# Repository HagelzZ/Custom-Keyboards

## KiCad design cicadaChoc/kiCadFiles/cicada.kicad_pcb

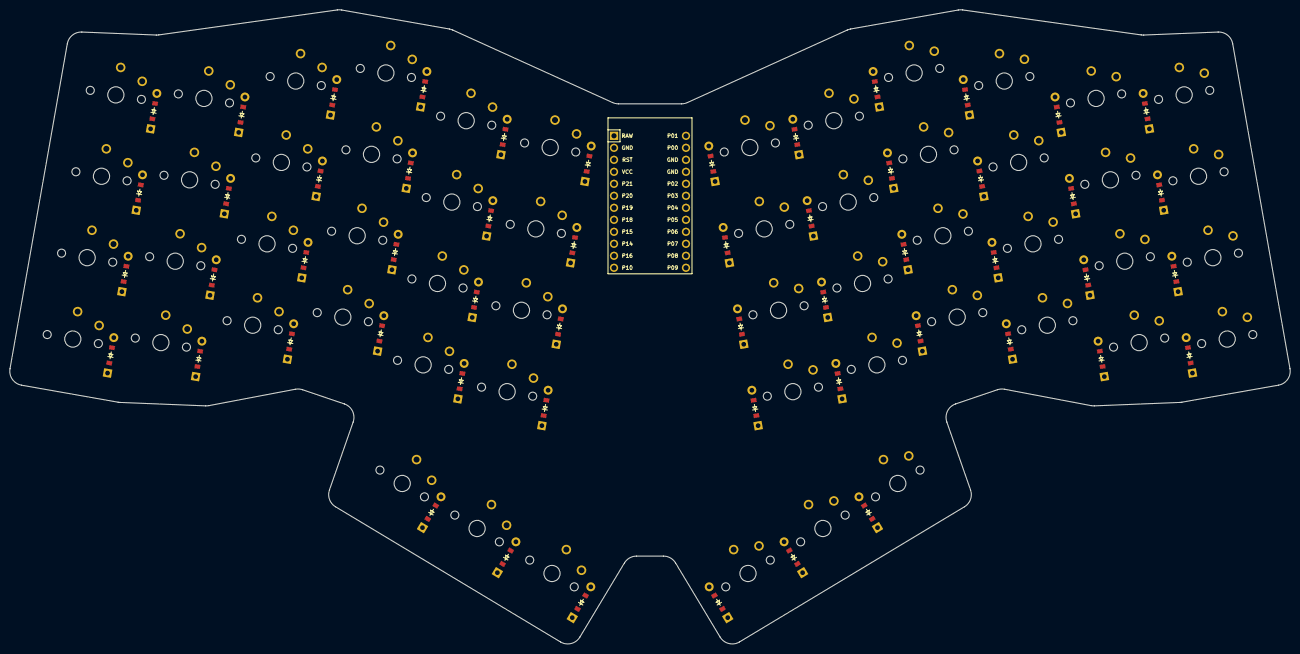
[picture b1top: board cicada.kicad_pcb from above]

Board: 2 copper layers, 271.1 x 134.3 mm, 109 parts (0 on the bottom side), 71 nets, no tracks yet.

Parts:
D1, D2, D3, D4, D5, D6, D7, D8, D9, D10, D11, D12, D13, D14, D15, D16, D17, D18, D19, D20, D21, D22, D23, D24, D25, D26, D27, D28, D29, D30, D31, D32, D33, D34, D35, D36, D37, D38, D39, D40, D41, D42, D43, D44, D45, D46, D47, D48, D49, D50, D51, D52, D53, D54: ComboDiode
MCU1: ProMicro
S1, S2, S3, S4, S5, S6, S7, S8, S9, S10, S11, S12, S13, S14, S15, S16, S17, S18, S19, S20, S21, S22, S23, S24, S25, S26, S27, S28, S29, S30, S31, S32, S33, S34, S35, S36, S37, S38, S39, S40, S41, S42, S43, S44, S45, S46, S47, S48, S49, S50, S51, S52, S53, S54: PG1350

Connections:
GND: MCU1.2, MCU1.15, MCU1.16
P0: MCU1.14, S17.1, S18.1, S19.1, S20.1, S26.1, S44.1, S45.1, S46.1, S47.1, S53.1
P1: MCU1.13, S21.1, S22.1, S23.1, S24.1, S27.1, S48.1, S49.1, S50.1, S51.1, S54.1
P2: MCU1.17, S13.1, S14.1, S15.1, S16.1, S25.1, S40.1, S41.1, S42.1, S43.1, S52.1
P3: MCU1.18, S9.1, S10.1, S11.1, S12.1, S36.1, S37.1, S38.1, S39.1
P5: D31.1, D35.1, D39.1, D43.1, D47.1, D51.1, MCU1.20
P6: D30.1, D34.1, D38.1, D42.1, D46.1, D50.1, MCU1.21
P7: D29.1, D33.1, D37.1, D41.1, D45.1, D49.1, MCU1.22
P8: D28.1, D32.1, D36.1, D40.1, D44.1, D48.1, MCU1.23
P9: D52.1, D53.1, D54.1, MCU1.24
P10: D25.1, D26.1, D27.1, MCU1.12
P14: D2.1, D6.1, D10.1, D14.1, D18.1, D22.1, MCU1.10
P15: D3.1, D7.1, D11.1, D15.1, D19.1, D23.1, MCU1.9
P16: D1.1, D5.1, D9.1, D13.1, D17.1, D21.1, MCU1.11
P18: D4.1, D8.1, D12.1, D16.1, D20.1, D24.1, MCU1.8
P20: MCU1.6, S1.1, S2.1, S3.1, S4.1, S28.1, S29.1, S30.1, S31.1
P21: MCU1.5, S5.1, S6.1, S7.1, S8.1, S32.1, S33.1, S34.1, S35.1
far_thumb: D27.2, S27.2
home_thumb: D26.2, S26.2
index_bottom: D17.2, S17.2
index_home: D18.2, S18.2
index_number: D20.2, S20.2
index_top: D19.2, S19.2
indexfar_bottom: D21.2, S21.2
indexfar_home: D22.2, S22.2
indexfar_number: D24.2, S24.2
indexfar_top: D23.2, S23.2
middle_bottom: D13.2, S13.2
middle_home: D14.2, S14.2
middle_number: D16.2, S16.2
middle_top: D15.2, S15.2
mirror_far_thumb: D54.2, S54.2
mirror_home_thumb: D53.2, S53.2
mirror_index_bottom: D44.2, S44.2
mirror_index_home: D45.2, S45.2
mirror_index_number: D47.2, S47.2
mirror_index_top: D46.2, S46.2
mirror_indexfar_bottom: D48.2, S48.2
mirror_indexfar_home: D49.2, S49.2
mirror_indexfar_number: D51.2, S51.2
mirror_indexfar_top: D50.2, S50.2
mirror_middle_bottom: D40.2, S40.2
mirror_middle_home: D41.2, S41.2
mirror_middle_number: D43.2, S43.2
mirror_middle_top: D42.2, S42.2
mirror_near_thumb: D52.2, S52.2
mirror_outer_bottom: D28.2, S28.2
mirror_outer_home: D29.2, S29.2
mirror_outer_number: D31.2, S31.2
mirror_outer_top: D30.2, S30.2
mirror_pinky_bottom: D32.2, S32.2
mirror_pinky_home: D33.2, S33.2
mirror_pinky_number: D35.2, S35.2
mirror_pinky_top: D34.2, S34.2
mirror_ring_bottom: D36.2, S36.2
mirror_ring_home: D37.2, S37.2
mirror_ring_number: D39.2, S39.2
mirror_ring_top: D38.2, S38.2
near_thumb: D25.2, S25.2
outer_bottom: D1.2, S1.2
outer_home: D2.2, S2.2
outer_number: D4.2, S4.2
outer_top: D3.2, S3.2
pinky_bottom: D5.2, S5.2
pinky_home: D6.2, S6.2
pinky_number: D8.2, S8.2
pinky_top: D7.2, S7.2
ring_bottom: D9.2, S9.2
ring_home: D10.2, S10.2
ring_number: D12.2, S12.2
ring_top: D11.2, S11.2

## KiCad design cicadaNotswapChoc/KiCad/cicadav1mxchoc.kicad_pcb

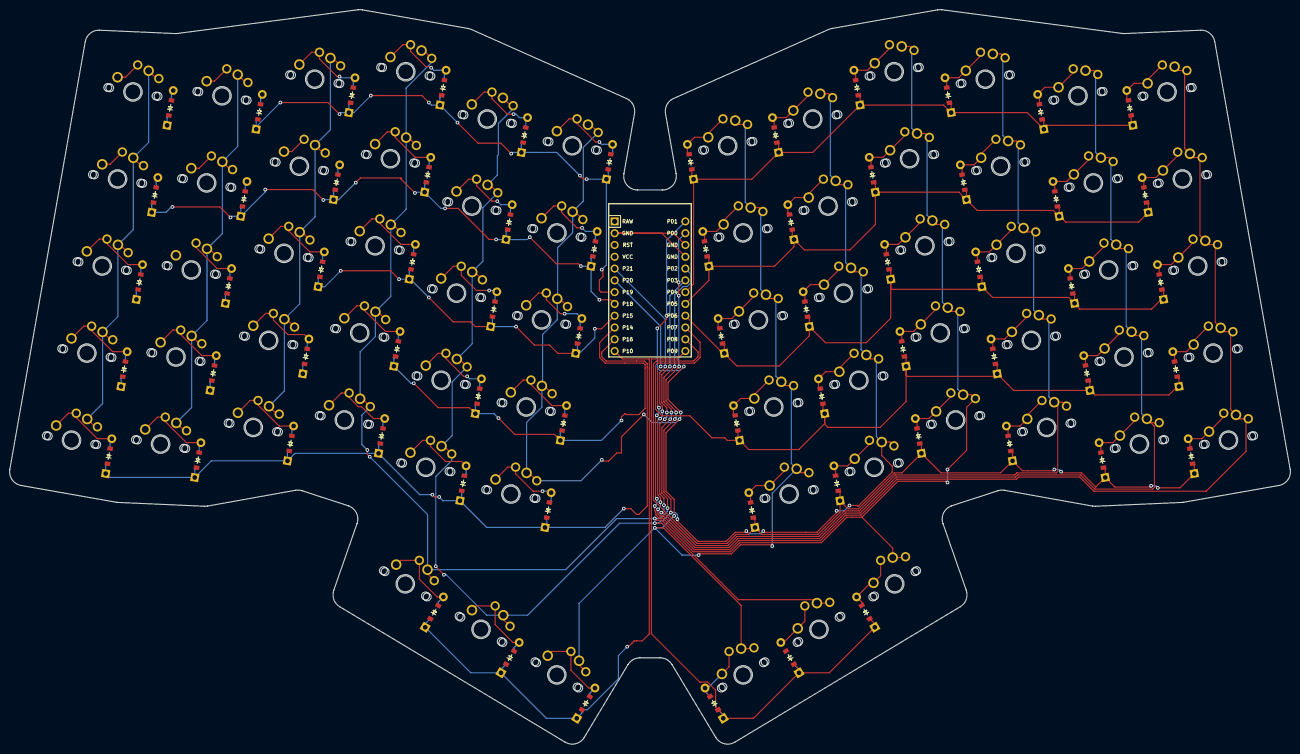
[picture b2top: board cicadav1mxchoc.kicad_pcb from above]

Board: 2 copper layers, 276.0 x 158.3 mm, 199 parts (0 on the bottom side), 85 nets.

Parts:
D1, D2, D3, D4, D5, D6, D7, D8, D9, D10, D11, D12, D13, D14, D15, D16, D17, D18, D19, D20, D21, D22, D23, D24, D25, D26, D27, D28, D29, D30, D31, D32, D33, D34, D35, D36, D37, D38, D39, D40, D41, D42, D43, D44, D45, D46, D47, D48, D49, D50, D51, D52, D53, D54, D55, D56, D57, D58, D59, D60, D61, D62, D63, D64, D65, D66: ComboDiode
MCU1: ProMicro
S1, S2, S3, S4, S5, S6, S7, S8, S9, S10, S11, S12, S13, S14, S15, S16, S17, S18, S19, S20, S21, S22, S23, S24, S25, S26, S27, S28, S29, S30, S31, S32, S33, S34, S35, S36, S37, S38, S39, S40, S41, S42, S43, S44, S45, S46, S47, S48, S49, S50, S51, S52, S53, S54, S55, S56, S57, S58, S59, S60, S61, S62, S63, S64, S65, S66: PG1350
S67, S68, S69, S70, S71, S72, S73, S74, S75, S76, S77, S78, S79, S80, S81, S82, S83, S84, S85, S86, S87, S88, S89, S90, S91, S92, S93, S94, S95, S96, S97, S98, S99, S100, S101, S102, S103, S104, S105, S106, S107, S108, S109, S110, S111, S112, S113, S114, S115, S116, S117, S118, S119, S120, S121, S122, S123, S124, S125, S126, S127, S128, S129, S130, S131, S132: MX

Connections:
GND: MCU1.2, MCU1.15, MCU1.16
P0: MCU1.14, S21.1, S22.1, S23.1, S24.1, S25.1, S32.1, S54.1, S55.1, S56.1, S57.1, S58.1, S65.1, S87.1, S88.1, S89.1, S90.1, S91.1, S98.1, S120.1, S121.1, S122.1, S123.1, S124.1, S131.1
P1: MCU1.13, S26.1, S27.1, S28.1, S29.1, S30.1, S33.1, S59.1, S60.1, S61.1, S62.1, S63.1, S66.1, S92.1, S93.1, S94.1, S95.1, S96.1, S99.1, S125.1, S126.1, S127.1, S128.1, S129.1, S132.1
P2: MCU1.17, S16.1, S17.1, S18.1, S19.1, S20.1, S31.1, S49.1, S50.1, S51.1, S52.1, S53.1, S64.1, S82.1, S83.1, S84.1, S85.1, S86.1, S97.1, S115.1, S116.1, S117.1, S118.1, S119.1, S130.1
P3: MCU1.18, S11.1, S12.1, S13.1, S14.1, S15.1, S44.1, S45.1, S46.1, S47.1, S48.1, S77.1, S78.1, S79.1, S80.1, S81.1, S110.1, S111.1, S112.1, S113.1, S114.1
P4: D38.1, D43.1, D48.1, D53.1, D58.1, D63.1, MCU1.19
P5: D37.1, D42.1, D47.1, D52.1, D57.1, D62.1, MCU1.20
P6: D36.1, D41.1, D46.1, D51.1, D56.1, D61.1, MCU1.21
P7: D35.1, D40.1, D45.1, D50.1, D55.1, D60.1, MCU1.22
P8: D34.1, D39.1, D44.1, D49.1, D54.1, D59.1, MCU1.23
P9: D64.1, D65.1, D66.1, MCU1.24
P10: D31.1, D32.1, D33.1, MCU1.12
P14: D2.1, D7.1, D12.1, D17.1, D22.1, D27.1, MCU1.10
P15: D3.1, D8.1, D13.1, D18.1, D23.1, D28.1, MCU1.9
P16: D1.1, D6.1, D11.1, D16.1, D21.1, D26.1, MCU1.11
P18: D4.1, D9.1, D14.1, D19.1, D24.1, D29.1, MCU1.8
P19: D5.1, D10.1, D15.1, D20.1, D25.1, D30.1, MCU1.7
P20: MCU1.6, S1.1, S2.1, S3.1, S4.1, S5.1, S34.1, S35.1, S36.1, S37.1, S38.1, S67.1, S68.1, S69.1, S70.1, S71.1, S100.1, S101.1, S102.1, S103.1, S104.1
P21: MCU1.5, S6.1, S7.1, S8.1, S9.1, S10.1, S39.1, S40.1, S41.1, S42.1, S43.1, S72.1, S73.1, S74.1, S75.1, S76.1, S105.1, S106.1, S107.1, S108.1, S109.1
far_thumb: D33.2, S33.2, S99.2
home_thumb: D32.2, S32.2, S98.2
index_bottom: D21.2, S21.2, S87.2
index_frow: D25.2, S25.2, S91.2
index_home: D22.2, S22.2, S88.2
index_number: D24.2, S24.2, S90.2
index_top: D23.2, S23.2, S89.2
indexfar_bottom: D26.2, S26.2, S92.2
indexfar_frow: D30.2, S30.2, S96.2
indexfar_home: D27.2, S27.2, S93.2
indexfar_number: D29.2, S29.2, S95.2
indexfar_top: D28.2, S28.2, S94.2
middle_bottom: D16.2, S16.2, S82.2
middle_frow: D20.2, S20.2, S86.2
middle_home: D17.2, S17.2, S83.2
middle_number: D19.2, S19.2, S85.2
middle_top: D18.2, S18.2, S84.2
mirror_far_thumb: D66.2, S66.2, S132.2
mirror_home_thumb: D65.2, S65.2, S131.2
mirror_index_bottom: D54.2, S54.2, S120.2
mirror_index_frow: D58.2, S58.2, S124.2
mirror_index_home: D55.2, S55.2, S121.2
mirror_index_number: D57.2, S57.2, S123.2
mirror_index_top: D56.2, S56.2, S122.2
mirror_indexfar_bottom: D59.2, S59.2, S125.2
mirror_indexfar_frow: D63.2, S63.2, S129.2
mirror_indexfar_home: D60.2, S60.2, S126.2
mirror_indexfar_number: D62.2, S62.2, S128.2
mirror_indexfar_top: D61.2, S61.2, S127.2
mirror_middle_bottom: D49.2, S49.2, S115.2
mirror_middle_frow: D53.2, S53.2, S119.2
mirror_middle_home: D50.2, S50.2, S116.2
mirror_middle_number: D52.2, S52.2, S118.2
mirror_middle_top: D51.2, S51.2, S117.2
mirror_near_thumb: D64.2, S64.2, S130.2
mirror_outer_bottom: D34.2, S34.2, S100.2
mirror_outer_frow: D38.2, S38.2, S104.2
mirror_outer_home: D35.2, S35.2, S101.2
mirror_outer_number: D37.2, S37.2, S103.2
mirror_outer_top: D36.2, S36.2, S102.2
mirror_pinky_bottom: D39.2, S39.2, S105.2
mirror_pinky_frow: D43.2, S43.2, S109.2
mirror_pinky_home: D40.2, S40.2, S106.2
mirror_pinky_number: D42.2, S42.2, S108.2
mirror_pinky_top: D41.2, S41.2, S107.2
mirror_ring_bottom: D44.2, S44.2, S110.2
mirror_ring_frow: D48.2, S48.2, S114.2
mirror_ring_home: D45.2, S45.2, S111.2
mirror_ring_number: D47.2, S47.2, S113.2
mirror_ring_top: D46.2, S46.2, S112.2
near_thumb: D31.2, S31.2, S97.2
outer_bottom: D1.2, S1.2, S67.2
outer_frow: D5.2, S5.2, S71.2
outer_home: D2.2, S2.2, S68.2
outer_number: D4.2, S4.2, S70.2
outer_top: D3.2, S3.2, S69.2
pinky_bottom: D6.2, S6.2, S72.2
pinky_frow: D10.2, S10.2, S76.2
pinky_home: D7.2, S7.2, S73.2
pinky_number: D9.2, S9.2, S75.2
pinky_top: D8.2, S8.2, S74.2
ring_bottom: D11.2, S11.2, S77.2
ring_frow: D15.2, S15.2, S81.2
ring_home: D12.2, S12.2, S78.2
ring_number: D14.2, S14.2, S80.2
ring_top: D13.2, S13.2, S79.2

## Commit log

2024-10-28 Creation Commit
    Nyello
2024-10-29 .gitignore, config.yaml and kicad files
2024-10-30 config.yaml updated & testpcb from ergogen
2024-10-30 config.yaml & pcb update
2024-10-30 pcb update
2024-11-01 pcb and config.yaml update
2024-11-05 config and pcb update
2024-11-06 keyb update
2024-11-06 yupdate
2024-11-06 config update
2024-11-06 oopdade
2024-11-07 config + pcb update
2024-11-07 Delete WIP/KiCad/cicadav1-backups directory
    deleted backups directory
2024-11-07 config + gitignore + pcb update
2024-11-12 Update fp-info-cache
2024-11-15 folder rename
2024-11-15 added mx/choc variant
2024-11-26 several different updates
